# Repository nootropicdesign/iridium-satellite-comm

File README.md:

# SAMD21 Arduino code for Iridium satellite communication using RockBLOCK 9603 modem

This repo has example code for the SAMD21-based Arduino code interfacing with a RockBLOCK 9603 satellite modem.

[See full project details](https://nootropicdesign.com/projectlab/2019/09/21/arduino-satellite-communication)

## Dependencies:

* [IridiumSBD library](https://github.com/mikalhart/IridiumSBD) - Arduino library for Iridium Short Data Burst messages
* [Adafruit GPS library](https://github.com/adafruit/Adafruit_GPS) - Arduino GPS library for NMEA sentence parsing
* [Adafruit ZeroTimer library](https://github.com/adafruit/Adafruit_ZeroTimer) - Timer library for SAMD21
* [Adafruit GFX library](https://github.com/adafruit/Adafruit-GFX-Library) - Core library for displays
* [Adafruit SSD1306 library](https://github.com/adafruit/Adafruit_SSD1306) - Library for our Monochrome OLEDs based on SSD1306 drivers

## Board Design

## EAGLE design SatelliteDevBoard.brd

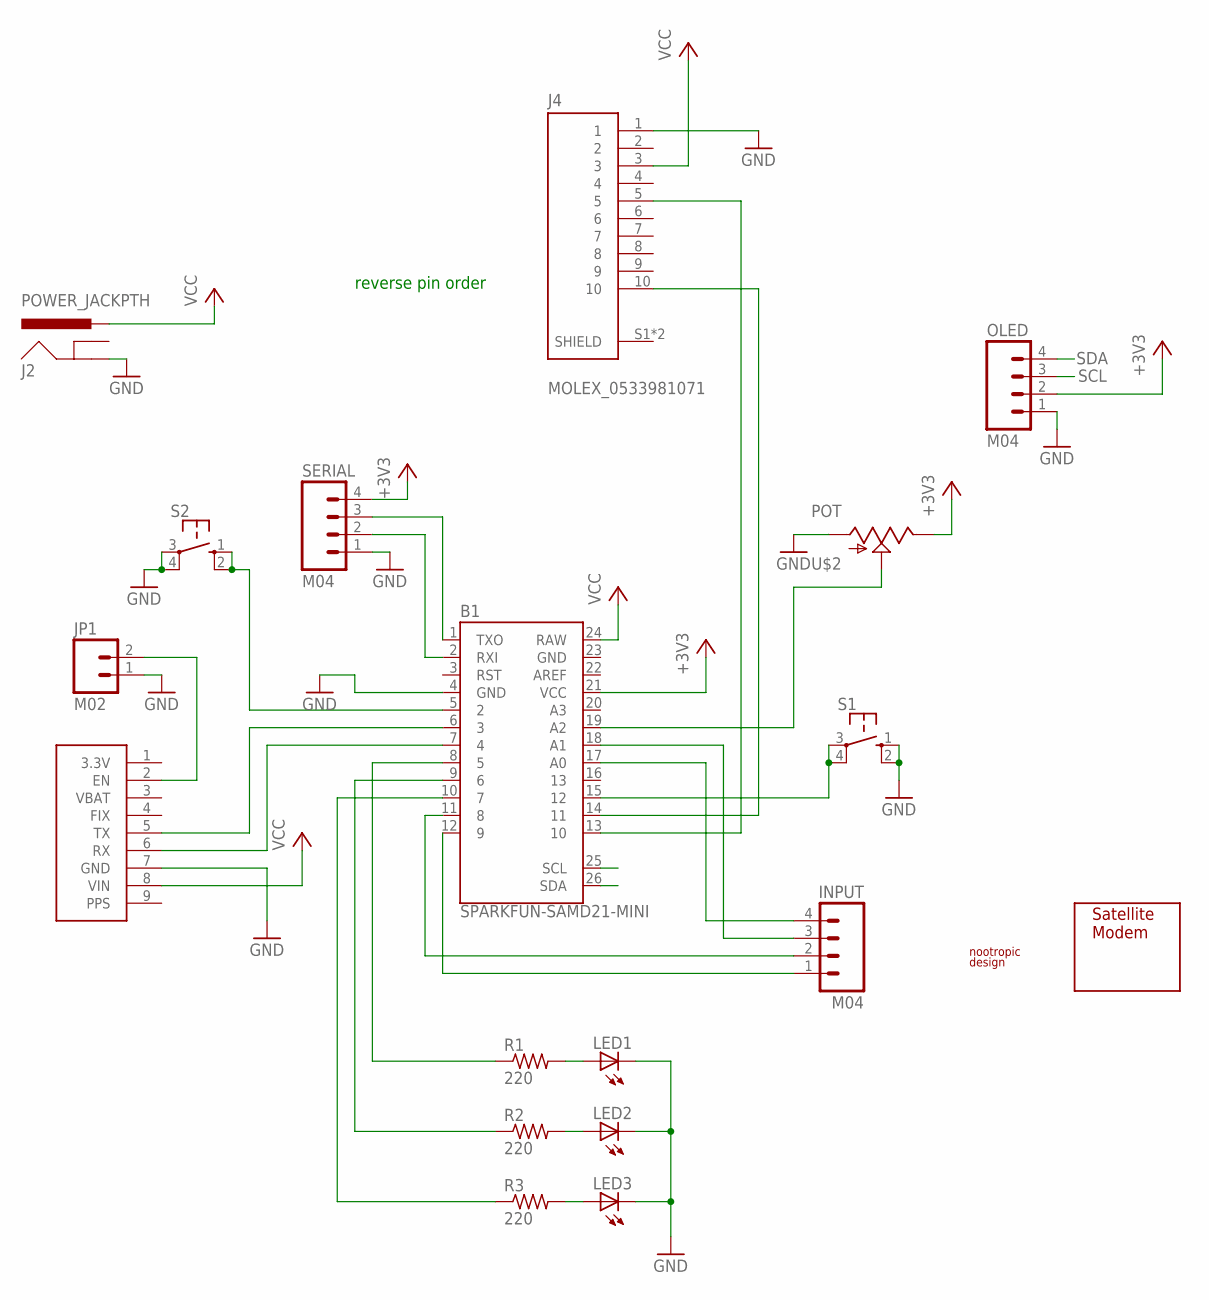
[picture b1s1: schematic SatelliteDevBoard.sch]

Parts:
B1: SPARKFUN-SAMD21-MINI
INPUT: M04; 1X04
J2: POWER_JACKPTH; POWER_JACK_PTH
J4: MOLEX_0533981071
JP1: M02; 1X02
LED1, LED2, LED3: LED3MM
OLED: M04; 1X04
R1, R2, R3: 220; 0207/10
S1, S2: SWITCH-TACT
SERIAL: M04; 1X04
U$1: ROCKBLOCK-9603
U$2: POT; TRIMMERPOT
U$3: ADAFRUIT-ULTIMATE-GPS-MODULE; ADAFRUIT-ULTIMATE-GPS
U$4: LOGO; LOGO_SMALL

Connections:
+3V3: B1.21 (VCC), OLED.2, SERIAL.4, U$2.3
A0: B1.17 (A0), INPUT.4
A1: B1.18 (A1), INPUT.3
D5: B1.8 (5), R1.1
D6: B1.9 (6), R2.1
D7: B1.10 (7), R3.1
D8: B1.11 (8), INPUT.2
D9: B1.12 (9), INPUT.1
D12: B1.15 (12), S1.3, S1.4 (P1)
GND: B1.4 (GND), B1.23 (GND), J2.GND, J4.1, JP1.1, LED1.K (C), LED2.K (C), LED3.K (C), OLED.1, S1.1 (S), S1.2 (S1), S2.3, S2.4 (P1), SERIAL.1, U$2.1, U$3.7 (GND)
MODEM_RX: B1.13 (10), J4.5
MODEM_TX: B1.14 (11), J4.10
unnamed: LED1.A, R1.2
unnamed: LED2.A, R2.2
unnamed: JP1.2, U$3.2 (EN)
unnamed: B1.6 (3), U$3.5 (TX)
unnamed: B1.7 (4), U$3.6 (RX)
unnamed: LED3.A, R3.2
unnamed: B1.5 (2), S2.1 (S), S2.2 (S1)
unnamed: B1.19 (A2), U$2.2 (WIPER)
RX: B1.2 (RXI), SERIAL.2
SCL: B1.25 (SCL), OLED.3
SDA: B1.26 (SDA), OLED.4
TX: B1.1 (TXO), SERIAL.3
VBAT: U$3.3 (VBAT)
VCC: B1.24 (RAW), J2.PWR, J4.3, U$3.8 (VIN)

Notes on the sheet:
reverse pin order

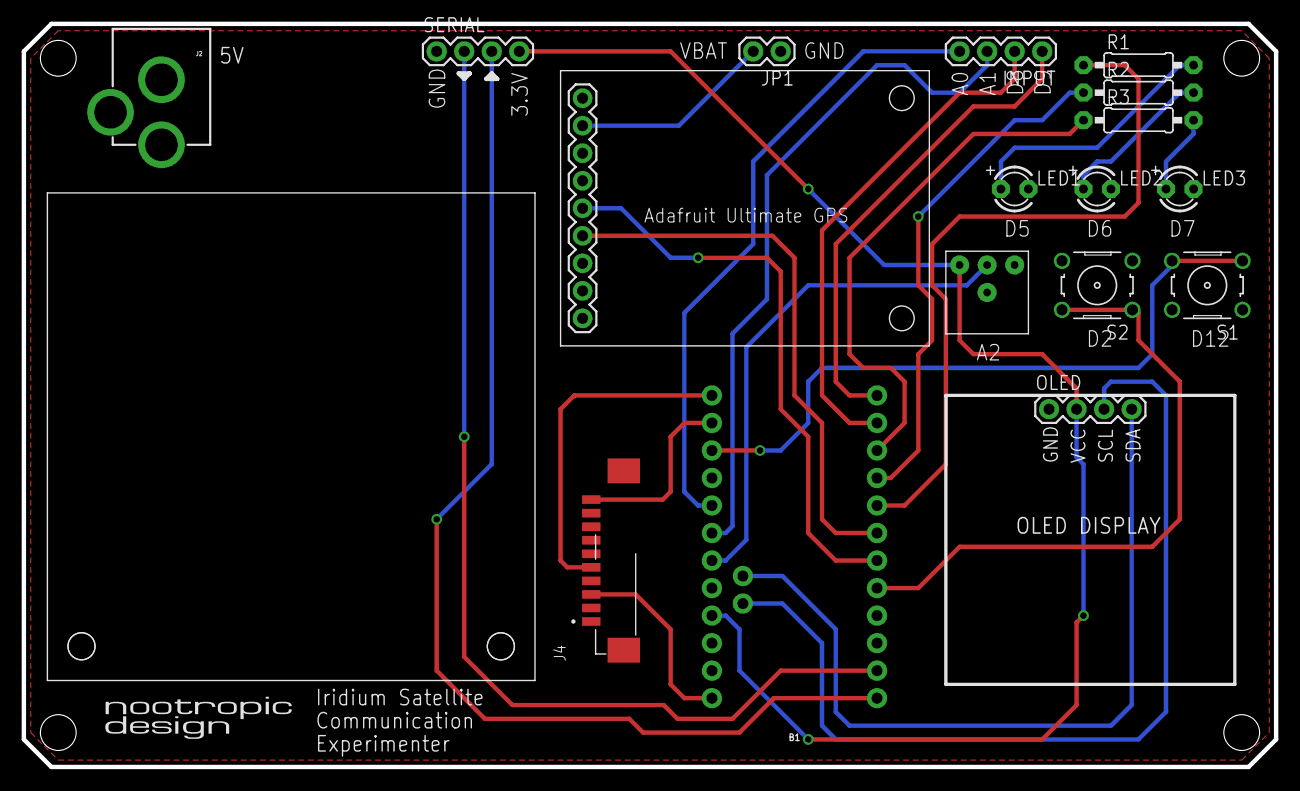
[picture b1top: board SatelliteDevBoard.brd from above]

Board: 2 copper layers, 115.6 x 68.6 mm, 19 parts (0 on the bottom side), 25 nets.

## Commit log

2019-09-22 Initial commit.
2019-09-23 Added Eagle files.
2019-09-24 Added schematic and board images.
2021-01-27 Updated constructor for Adafruit_SSD1306 display.
